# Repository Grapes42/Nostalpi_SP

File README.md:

# Gamepi SP
## Parts list
### PB Tech
|Part|Cost|
|-|-|
|[Pi Zero 2](https://www.pbtech.co.nz/product/SEVRBP0360/Raspberry-Pi-Zero-2-W-ARM-64-bit-Cortex-A53-CPU-51?src=raspberrypi)|$32.15|
|||

### Adafruit
|Part|Cost|
|-|-|
|[Powerboost 1000C](https://www.adafruit.com/product/2465)|$19.95|
|||

### Aliexpress
|Part|Cost|
|-|-|
|[GBA SP Replacement Shell](https://www.aliexpress.com/w/wholesale-gba-sp-shell.html?spm=a2g0o.productlist.search.0) (pick whatever one you like)|~$10|
|[LiPo Battery](https://www.aliexpress.com/item/1005007352024629.html?spm=a2g0o.productlist.main.9.352132357yHQEw&algo_pvid=9abd0122-2251-4358-a813-dd751d955b94&algo_exp_id=9abd0122-2251-4358-a813-dd751d955b94-4&pdp_npi=4%40dis%21NZD%214.42%212.65%21%21%2118.52%2111.11%21%402101fb1617223005320095233ea4d0%2112000040387142754%21sea%21NZ%216022188871%21X&curPageLogUid=StPAqdPkg6Pl&utparam-url=scene%3Asearch%7Cquery_from%3A)|~$4|

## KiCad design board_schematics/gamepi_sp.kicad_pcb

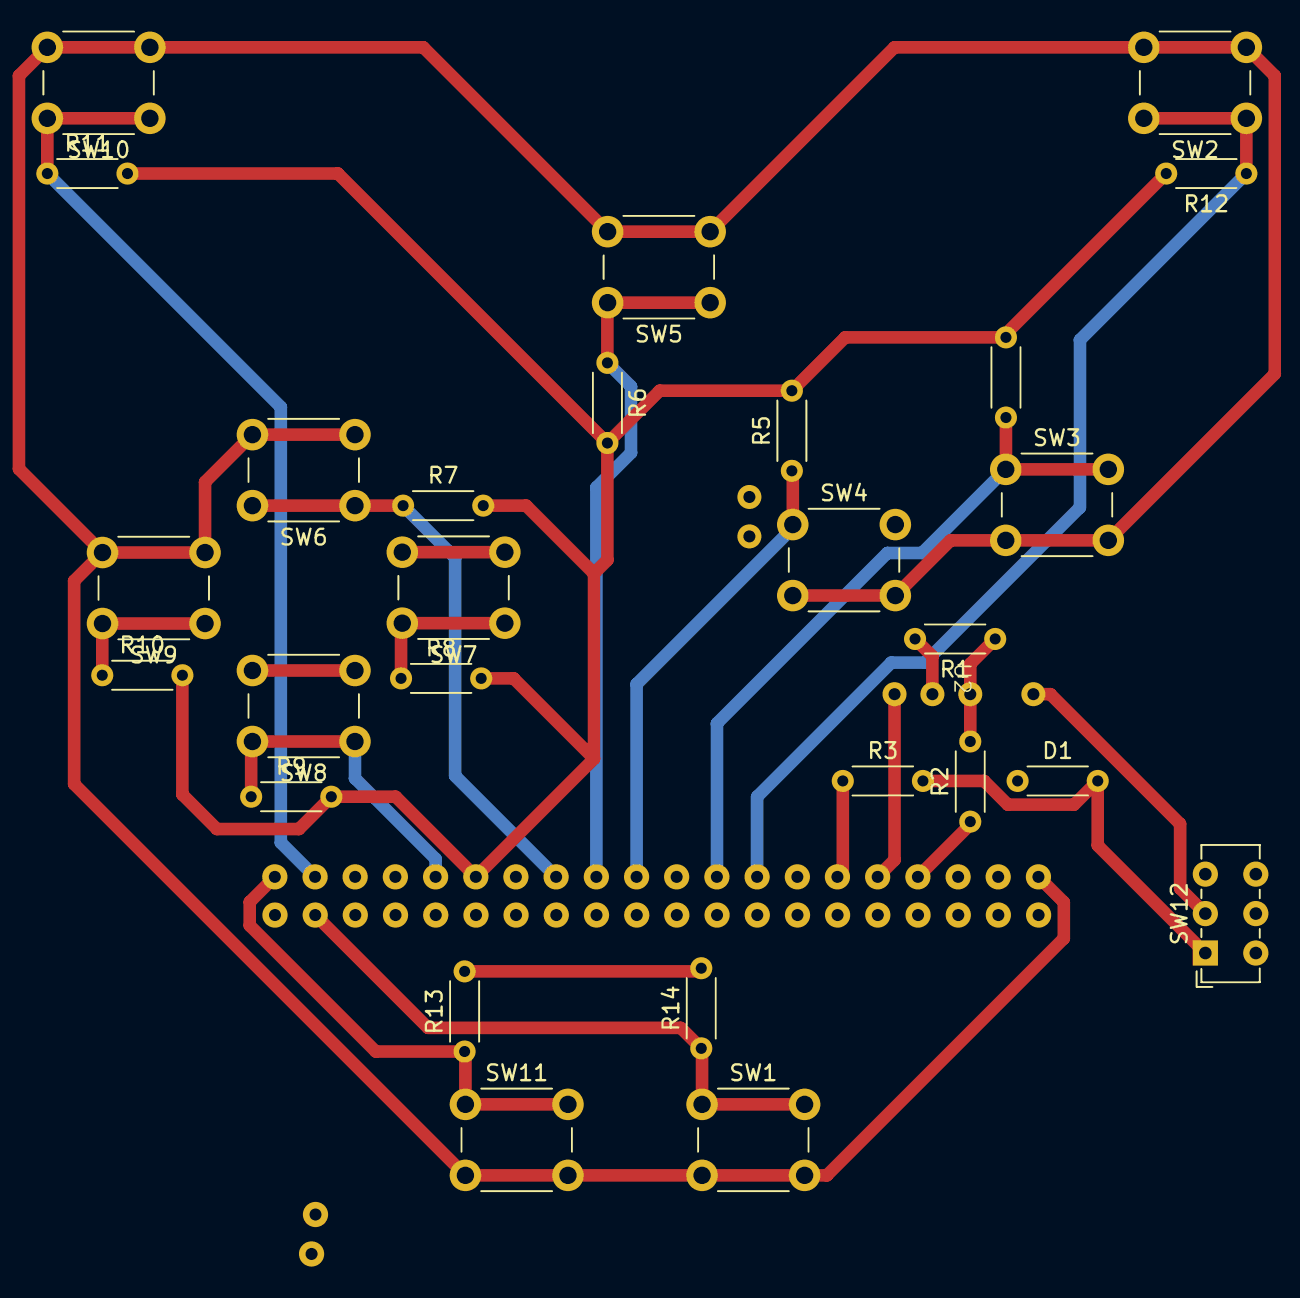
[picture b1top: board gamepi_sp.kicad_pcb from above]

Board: 2 copper layers, 29 parts (0 on the bottom side), 22 nets.

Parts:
D1: D; R_Axial_DIN0204_L3.6mm_D1.6mm_P5.08mm_Horizontal
R1: 100KΩ; R_Axial_DIN0204_L3.6mm_D1.6mm_P5.08mm_Horizontal
R2, R3: 10KΩ; R_Axial_DIN0204_L3.6mm_D1.6mm_P5.08mm_Horizontal
R4, R5, R6, R7, R8, R9, R10, R11, R12, R13, R14: 100k; R_Axial_DIN0204_L3.6mm_D1.6mm_P5.08mm_Horizontal
SW1: LED; SW_PUSH_6mm
SW2: UP; SW_PUSH_6mm
SW3: DOWN; SW_PUSH_6mm
SW4: LEFT; SW_PUSH_6mm
SW5: RIGHT; SW_PUSH_6mm
SW6: A; SW_PUSH_6mm
SW7: B; SW_PUSH_6mm
SW8: START; SW_PUSH_6mm
SW9: SELECT; SW_PUSH_6mm
SW10: R; SW_PUSH_6mm
SW11: L; SW_PUSH_6mm
SW12: Power Switch; SW_E-Switch_EG1271_SPDT
U1: pi_zero_pcb_pins
U2: powerboost_1000C_pins

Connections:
unnamed: D1.2 (A), R3.2, SW12.1 (A)
unnamed: D1.1 (K), R1.1, R2.2, U2.2 (EN)
unnamed: R4.2, R5.2, R6.2, R7.2, R8.2, R9.2, R10.2, R11.2, R12.2, R13.2, R14.2, U1.30 (GND)
unnamed: SW1.2, SW2.2, SW3.2, SW4.2, SW5.2, SW6.2, SW7.2, SW8.2, SW9.2, SW10.2, SW11.2, U1.2 (5V)
unnamed: SW12.2 (B), U2.1 (BAT)
unnamed: R8.1, SW7.1, U1.28 (GPIO_1)
unnamed: R7.1, SW6.1, U1.26 (GPIO_7)
unnamed: R6.1, SW5.1, U1.24 (GPIO_8)
unnamed: R9.1, SW8.1, U1.32 (GPIO_12)
unnamed: R2.1, U1.8 (GPIO_14)
unnamed: U1.10 (GPIO_15), U2.4 (LB)
unnamed: R10.1, SW9.1, U1.36 (GPIO_16)
unnamed: R3.1, U1.12 (GPIO_18)
unnamed: R11.1, SW10.1, U1.38 (GPIO_20)
unnamed: R13.1, SW11.1, U1.40 (GPIO_21)
unnamed: R12.1, SW2.1, U1.16 (GPIO_23)
unnamed: R4.1, SW3.1, U1.18 (GPIO_24)
unnamed: R5.1, SW4.1, U1.22 (GPIO_25)
unnamed: R14.1, SW1.1, U1.37 (GPIO_26)
unnamed: R1.2, U2.3 (GND)
unnamed: U1.43, U2.5 (Supply_5V)
unnamed: U1.44, U2.6 (Supply_GND)

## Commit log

2024-06-14 moved my custom pcb parts from my other project Duckey
2024-06-17 fixed my imports
2024-06-17 designed circuit for powerboost 1000c, courtesy of Daniel Bull's open source circuit on github
2024-06-17 added controler buttons to schematic
2024-06-20 started documentation for assesment
2024-06-21 more work on documentation
2024-06-24 adding to documentation
2024-06-25 adding to readme
2024-06-25 changed schematic from push button to slideswitch layout
2024-06-26 pcb design is hard :c
2024-06-26 restarting pcb layout with new approach
2024-06-26 another pcb attempt, this time more succesful
2024-06-26 pcb design that i am happy with
2024-07-21 added future opportunities to docs
2024-08-23 added proposed diagrams in documentation
2024-08-23 updated milestones
2024-08-23 updated computers comparison
2024-08-23 risks and mitigations
2024-08-27 added critiquing
2024-08-28 more documentation stuff
2024-08-29 added more to the project focus
2024-08-31 working on refined project focus
2024-08-31 yet more work on refined project focus
2024-09-01 little logo courtesy of my gf
2024-09-01 cleaned up, and added sources
2024-09-01 finished mostly! now to check everything and hand in
